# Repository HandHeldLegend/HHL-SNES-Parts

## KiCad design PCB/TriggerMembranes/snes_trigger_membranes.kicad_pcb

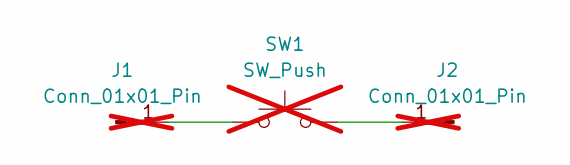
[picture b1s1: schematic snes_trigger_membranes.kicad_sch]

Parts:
J1, J2: Conn_01x01_Pin; PinHeader_1x01_P1.27mm_Vertical; not fitted
SW1: SW_Push; progcc_bpad; not fitted

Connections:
unnamed: J1.1, SW1.2
unnamed: J2.1, SW1.1

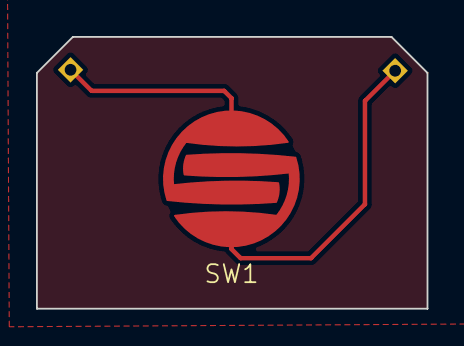
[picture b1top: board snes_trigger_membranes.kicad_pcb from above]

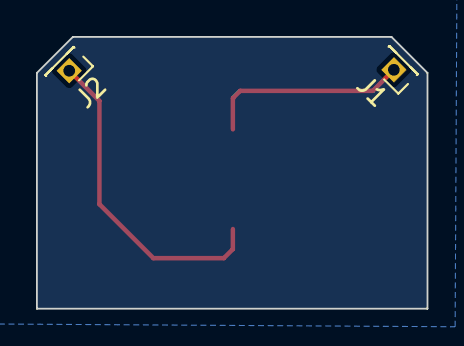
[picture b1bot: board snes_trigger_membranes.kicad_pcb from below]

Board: 2 copper layers, 21.7 x 15.1 mm, 3 parts (2 on the bottom side), 2 nets.

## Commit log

2023-09-26 PCB Update
